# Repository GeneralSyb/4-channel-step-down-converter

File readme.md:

A simple 4-channel step-down converter I am using for my telescope to supply power to multiple devices at different voltages from a 19.5V powersupply
It also has space for the components for a DIY electronic focuser(WeMos ESP32-S2 Mini, EasyDrive)

It uses 4 of these step-down converter which should be able to output about 1A.

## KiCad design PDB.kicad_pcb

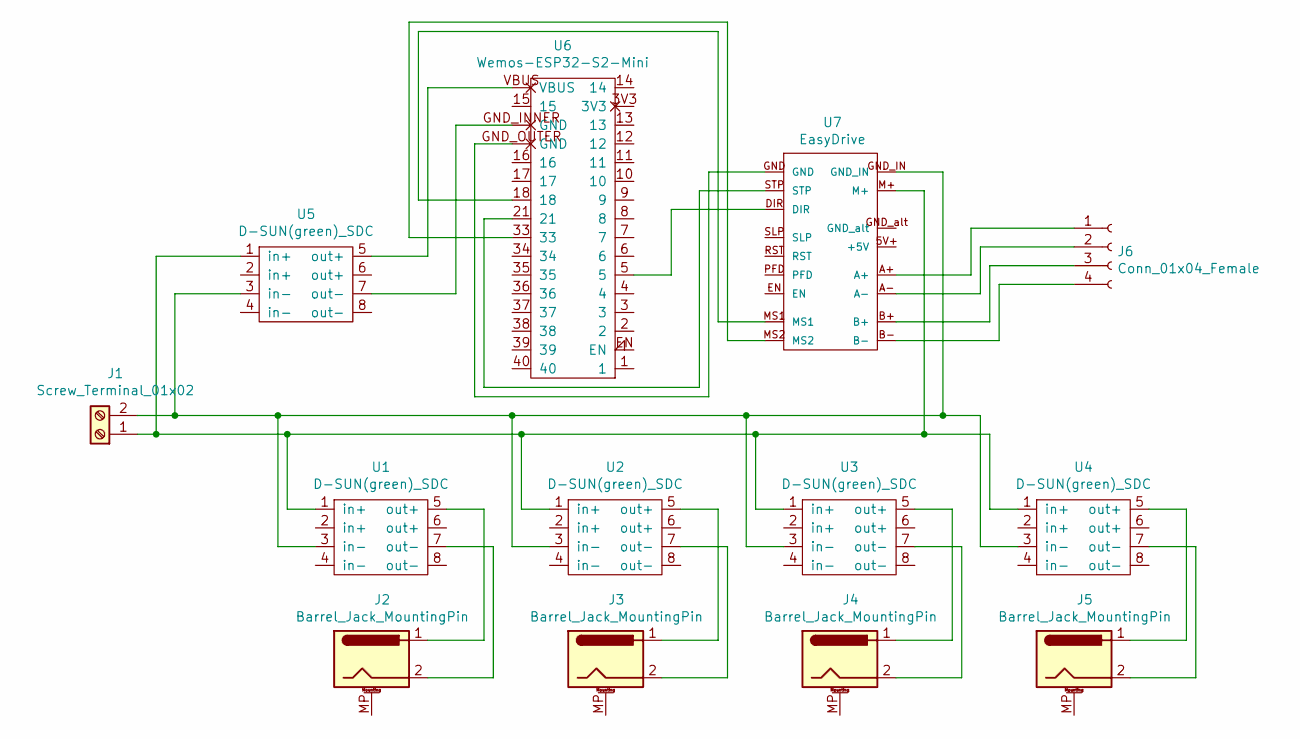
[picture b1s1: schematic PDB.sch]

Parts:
J1: Screw_Terminal_01x02; TerminalBlock_Phoenix_MKDS-1,5-2-5.08_1x02_P5.08mm_Horizont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
J2, J3, J4, J5: Barrel_Jack_MountingPin; BarrelJack_Horizontal
J6: Conn_01x04_Female; JST_PH_B4B-PH-K_1x04_P2.00mm_Vertical
U1, U2, U3, U4, U5: D-SUN(green)_SDC; D-SUN(green) SDC
U6: Wemos-ESP32-S2-Mini; Wemos ESP-32 S2 Mini
U7: EasyDrive; EasyDriver

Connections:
unnamed: J1.1, U1.1 (in+), U2.1 (in+), U3.1 (in+), U4.1 (in+), U5.1 (in+), U7.M+
unnamed: J1.2, U1.3 (in-), U2.3 (in-), U3.3 (in-), U4.3 (in-), U5.3 (in-), U7.GND_IN
unnamed: J2.1, U1.5 (out+)
unnamed: J2.2, U1.7 (out-)
unnamed: J3.1, U2.5 (out+)
unnamed: J3.2, U2.7 (out-)
unnamed: J4.1, U3.5 (out+)
unnamed: J4.2, U3.7 (out-)
unnamed: J5.1, U4.5 (out+)
unnamed: J5.2, U4.7 (out-)
unnamed: J6.1, U7.A+
unnamed: J6.2, U7.A-
unnamed: J6.3, U7.B+
unnamed: J6.4, U7.B-
unnamed: U5.5 (out+), U6.VBUS
unnamed: U5.7 (out-), U6.GND_INNER (GND)
unnamed: U6.5, U7.DIR
unnamed: U6.18, U7.MS1
unnamed: U6.21, U7.STP
unnamed: U6.33, U7.MS2
unnamed: U6.GND_OUTER (GND), U7.GND

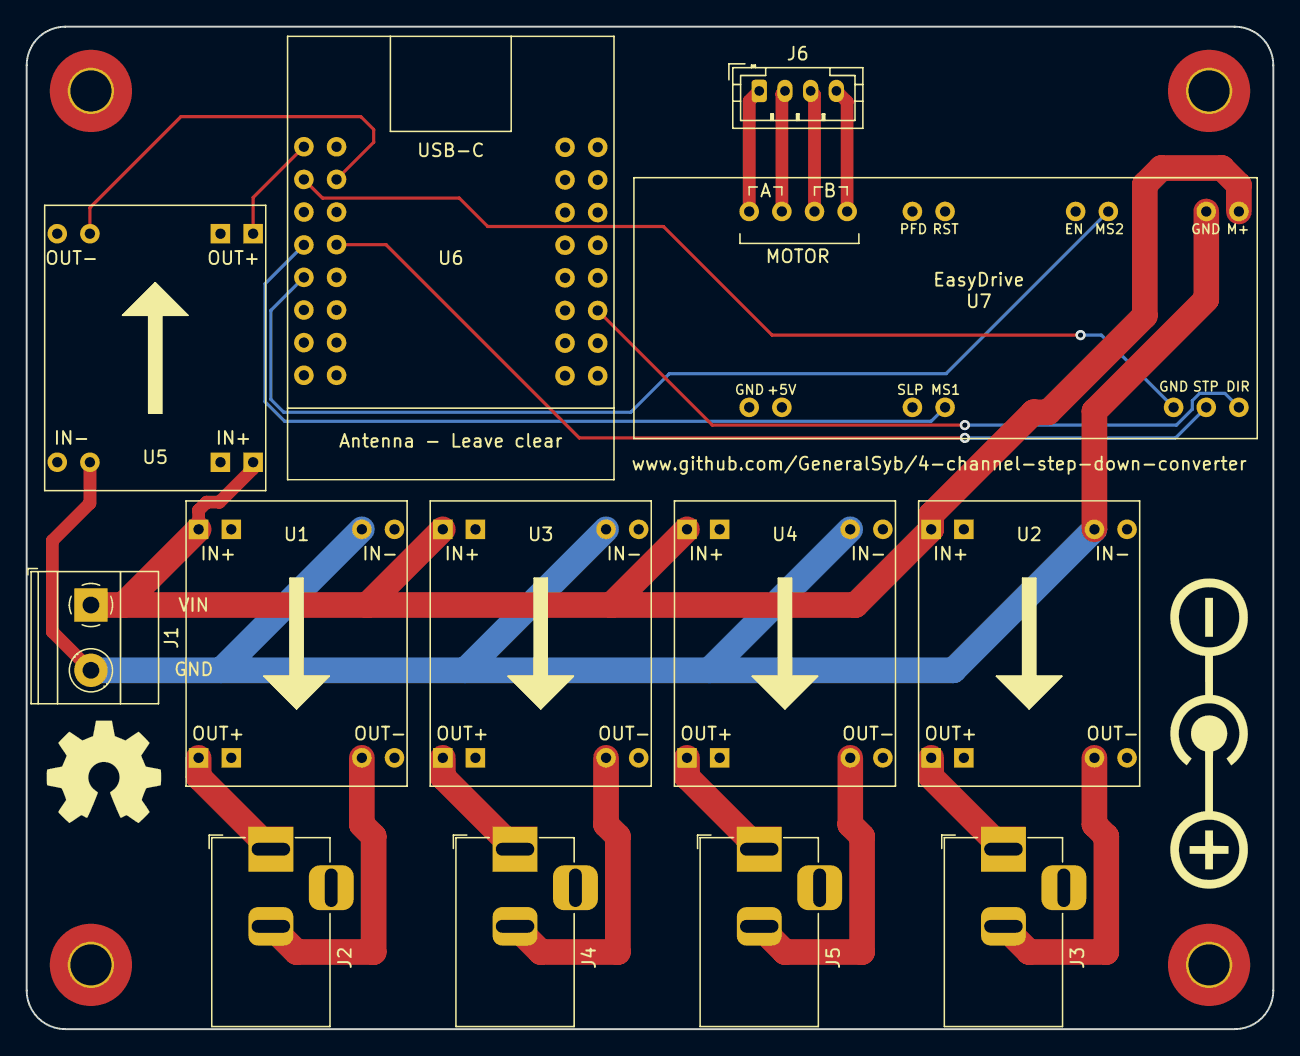
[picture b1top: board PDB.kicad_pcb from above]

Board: 2 copper layers, 97.0 x 78.0 mm, 13 parts (0 on the bottom side), 21 nets.
